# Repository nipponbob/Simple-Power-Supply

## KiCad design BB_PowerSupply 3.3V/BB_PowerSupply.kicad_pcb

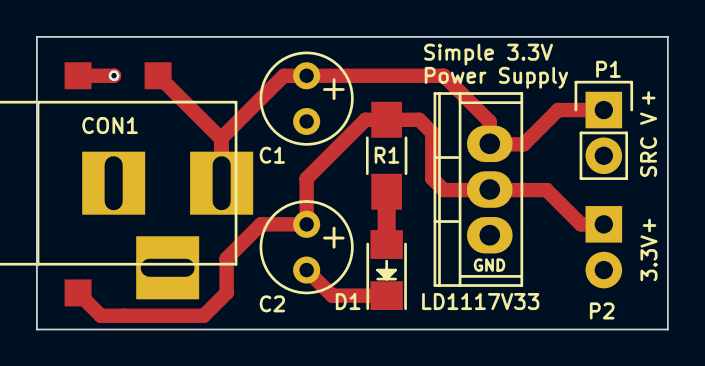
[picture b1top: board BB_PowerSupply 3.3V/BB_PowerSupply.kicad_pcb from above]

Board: 2 copper layers, 35.1 x 16.3 mm, 11 parts (1 on the bottom side), 4 nets.

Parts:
C1: 0.1uF; Elko_vert_11x5mm_RM2.5
C2: 10uF; Elko_vert_11x5mm_RM2.5
CON1: BARREL_JACK
D1: LED; LED-1206
LD1117V33: LD1117V33; TO-220
P1: 5V Out; Socket_Strip_Straight_1x02
P2: 3.3V Out; Pin_Header_Straight_1x02
R1: 56; R_1206_HandSoldering
TST1: +5v TST; Measurement_Point_Square-SMD-Pad_Small
TST2: Gnd TST; Measurement_Point_Square-SMD-Pad_Small
TST3: 3.3V TST; Measurement_Point_Square-SMD-Pad_Small

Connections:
+5V: C1.1, CON1.1, LD1117V33.3, P1.1, TST1.1
GND: C1.2, C2.2, CON1.2, CON1.3, D1.1, LD1117V33.1, P1.2, P2.2, TST2.1
unnamed: C2.1, LD1117V33.2, P2.1, R1.1, TST3.1
unnamed: D1.2, R1.2

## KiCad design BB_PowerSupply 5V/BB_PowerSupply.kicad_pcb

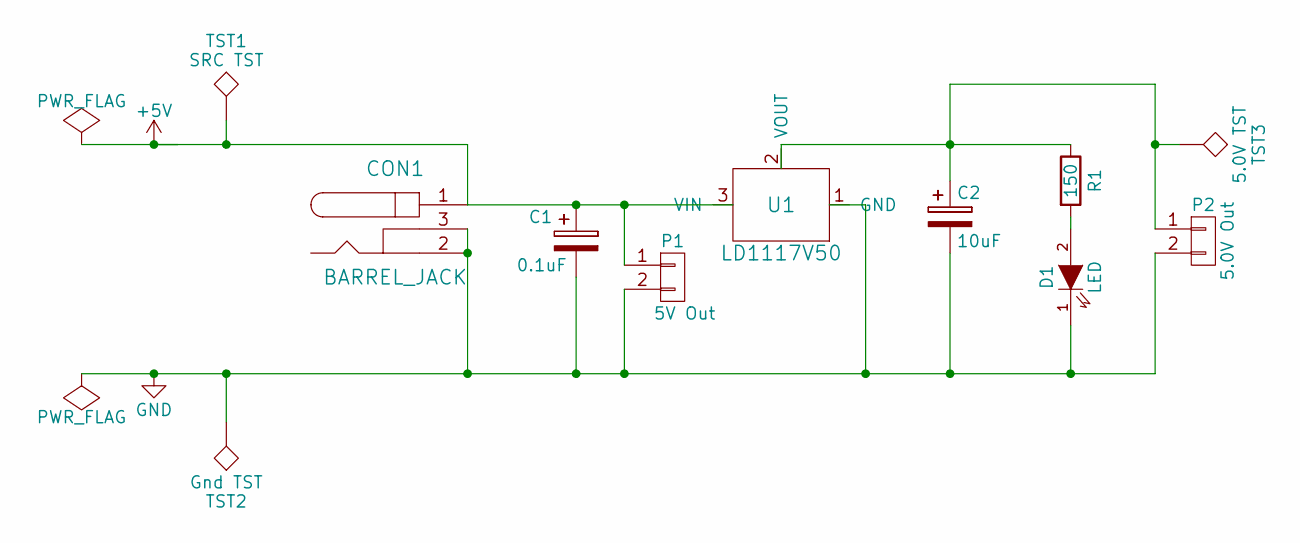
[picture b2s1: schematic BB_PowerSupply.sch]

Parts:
C1: 0.1uF; Elko_vert_11x5mm_RM2.5
C2: 10uF; Elko_vert_11x5mm_RM2.5
CON1: BARREL_JACK
D1: LED; LED-1206
P1: 5V Out; Socket_Strip_Straight_1x02
P2: 5.0V Out; Pin_Header_Straight_1x02
R1: 150; R_1206_HandSoldering
TST1: SRC TST; Measurement_Point_Square-SMD-Pad_Small
TST2: Gnd TST; Measurement_Point_Square-SMD-Pad_Small
TST3: 5.0V TST; Measurement_Point_Square-SMD-Pad_Small
U1: LD1117V50; TO-220

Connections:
+5V: C1.1, CON1.1, P1.1, TST1.1, U1.3 (VIN); also elsewhere on the board
GND: C1.2, C2.2, CON1.2, CON1.3, D1.1 (K), P1.2, P2.2, TST2.1, U1.1 (GND); also elsewhere on the board
unnamed 2: C2.1, P2.1, R1.1, TST3.1, U1.2 (VOUT); also elsewhere on the board
unnamed: D1.2 (A), R1.2

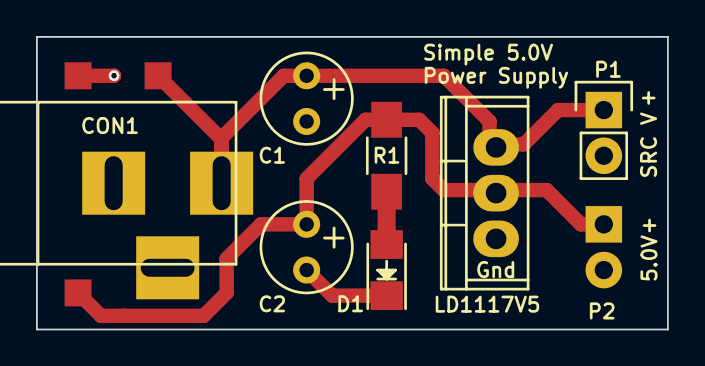
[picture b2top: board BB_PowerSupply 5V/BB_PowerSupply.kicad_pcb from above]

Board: 2 copper layers, 35.1 x 16.3 mm, 11 parts (1 on the bottom side), 4 nets.

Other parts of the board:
LD1117V5: LD1117V50; TO-220

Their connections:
+5V: LD1117V5.3; also elsewhere on the board
GND: LD1117V5.1; also elsewhere on the board
unnamed 2: LD1117V5.2; also elsewhere on the board

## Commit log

2015-08-21 Initial commit - All files added - gerbers to be added later
